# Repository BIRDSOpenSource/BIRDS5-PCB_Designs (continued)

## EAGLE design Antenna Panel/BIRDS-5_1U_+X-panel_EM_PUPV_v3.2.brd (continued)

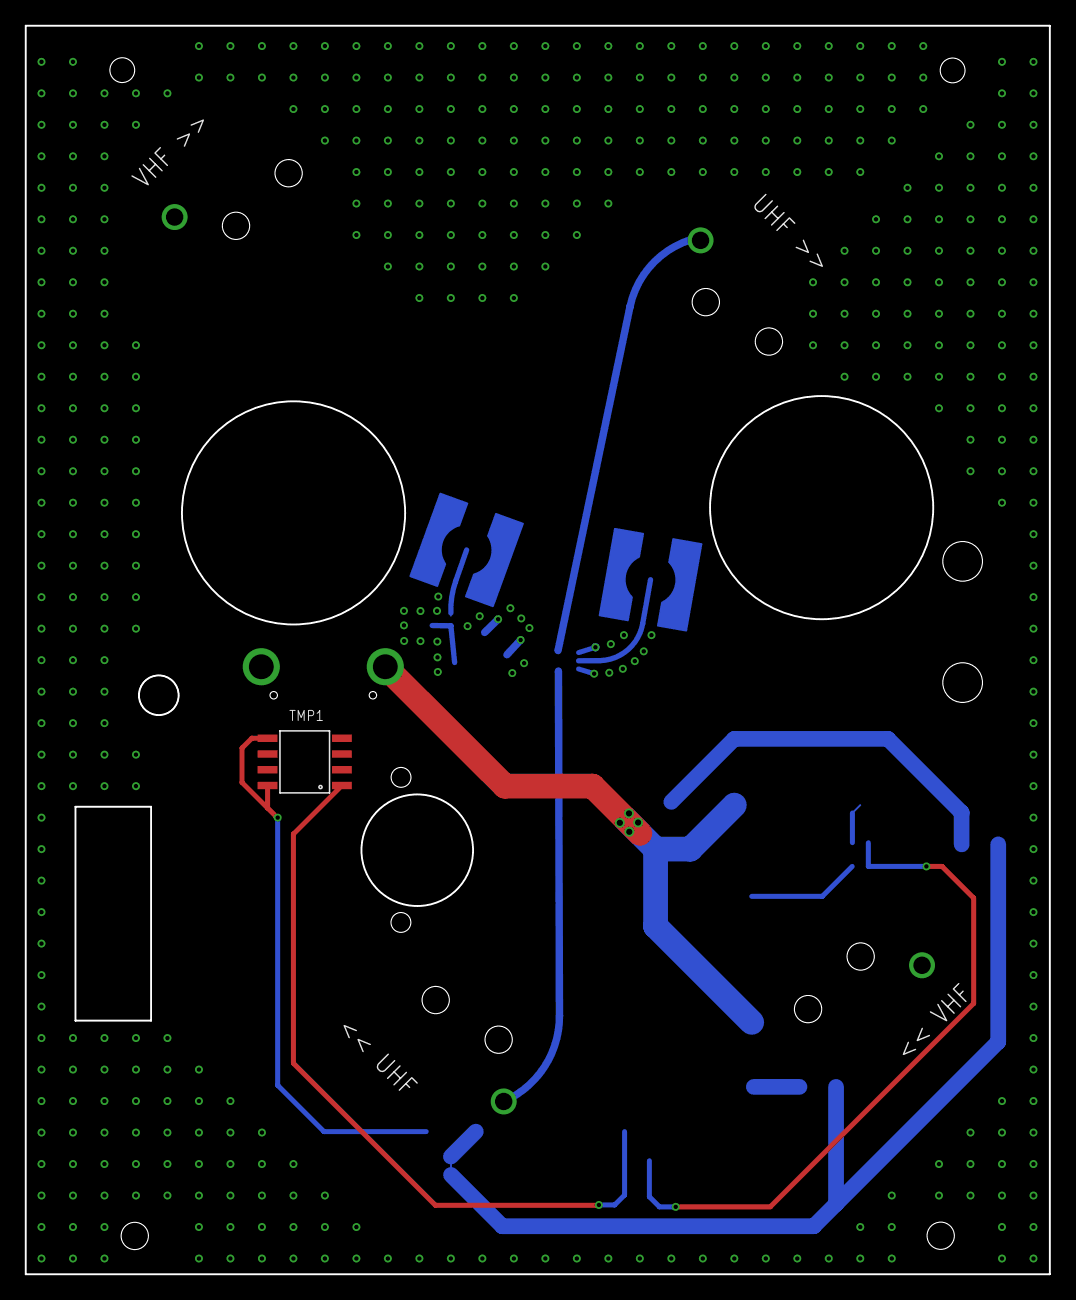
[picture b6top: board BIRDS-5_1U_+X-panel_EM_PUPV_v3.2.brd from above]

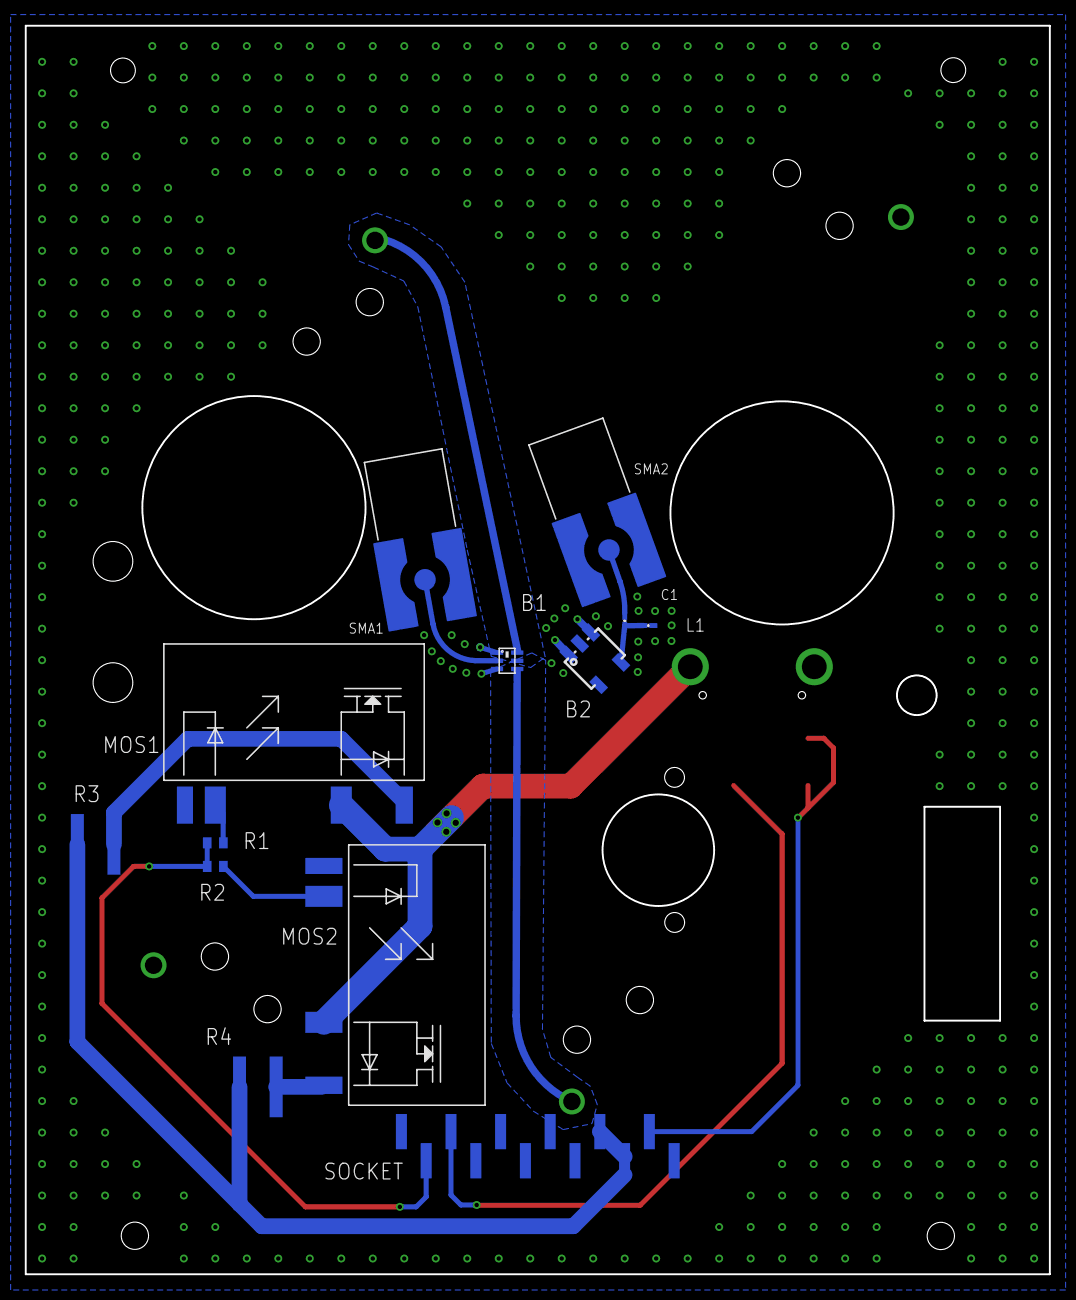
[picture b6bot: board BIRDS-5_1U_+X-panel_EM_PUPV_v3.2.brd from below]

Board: 4 copper layers, 82.6 x 100.7 mm, 20 parts (13 on the bottom side), 17 nets.
